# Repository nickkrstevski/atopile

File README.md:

# atopile

Compiler for hardware - starting with PCBs

## Usage

There's not a lot here, because it's over at http://docs.atopile.io/

## Development

### Prerequisites / Installation

You'll need >= `python3.10` and `pip` (Use `brew`).

I'd strongly recommend developing within a `venv`

Since we'll be using this `venv` for both work within this tool directory and whatever projects you're using it on, I'd recommend creating something along the lines of an `atopile-workspace` or `ato-ws` directory somewhere, and then creating a `venv` in there. This means if you do something like a `git clean -xdf` to remove crud, you won't blow away your `venv` with it.

If you decide to follow this, you'll end up with something like this:

```
atopile-workspace
├── .venv --> your virtual environment
├── atopile --> this repo
├── atopile.code-workspace --> vscode workspace file
└── bike-light --> project using atopile
```

Clone this repo.

Wherever you stick the `venv`, you can create the venv with  `python3.11 -m venv .venv` and then `source .venv/bin/activate`

For cli development (so practically all the time) : `pip install -e ."`

You'll need `npm` for front-end development (`brew install node`).

For any front-end development, you'll also need to install the front-end dependencies: `npm install`

## CLI development

ANTLR (or more specifically Java) was a PITA to get working on my Mac... so, I didn't 🤷‍♂️, I just wrapped up ANTLR in a neat little dockerised bundle and make a script that calls out to it easily.

As of writing, that lives in [mawildoer/antlr4](https://github.com/mawildoer/antlr4/tree/mawildoer/simplified-portable-docker/docker-simplified), but [hopefully we can get it into ANTLR mainline](https://github.com/antlr/antlr4/pull/4244) soon.

For now, clone the branch in the first link (eg. to your "repos" or "projects" directory), and then follow the [instructions](https://github.com/mawildoer/antlr4/tree/mawildoer/simplified-portable-docker/docker-simplified) on how to build it.

You can build the grammer to python source with the following command (modified with the appropriate paths for you).

`cd src/atopile/parser`

`/Users/mattwildoer/Projects/antlr4/docker-simplified/antlr4 -Dlanguage=Python3 -visitor AtopileParser.g4 AtopileLexer.g4`

## Front end development

To check out front-end changes live, run `npm run serve` in one terminal and make sure to run `ato view` on a project in another (to provide API access).

This will start the front-end server at `localhost:1234` and the backend at `localhost:2860`. The front-end's development server (`pracel`) will proxy API requests to the backend.

## Syntax highlighting is pretty nice...

You can download the extension from CI here:

Then, from your PC `code --install-extension path/to/atopile-*.vsix`

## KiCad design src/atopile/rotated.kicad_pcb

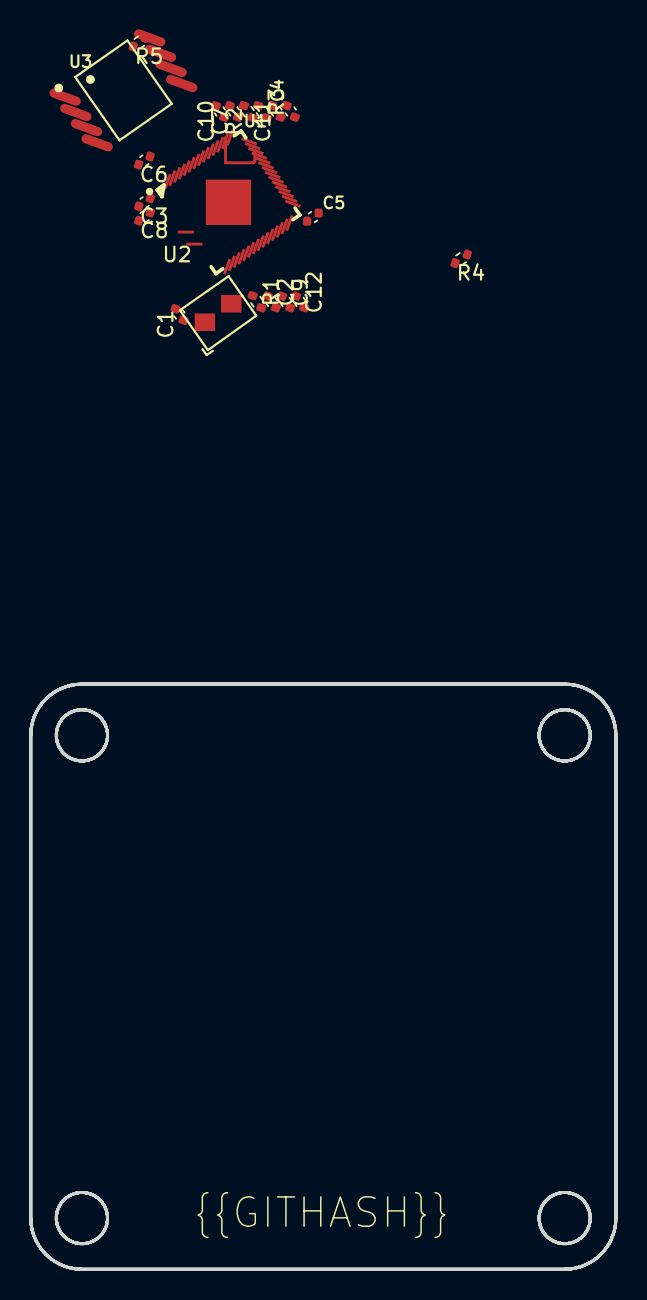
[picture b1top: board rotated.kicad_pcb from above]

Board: 2 copper layers, 40.0 x 40.0 mm, 20 parts (0 on the bottom side), 15 nets.

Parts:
C1, C2: 20pF; C0402
C3, C4, C5, C6, C7, C9, C10, C11: 100nF; C0402
C8, C12: 1uF; C0402
R1: 1k; R0402
R2, R3: 27R; R0402
R4, R5: 10k; R0402
U1: <help! no value>; LQFN-56_L7.0-W7.0-P0.4-EP
U2: <help! no value>; OSC-SMD_4P-L3.2-W2.5-BL
U3: <help! no value>; SOIC-8_L5.3-W5.3-P1.27-LS8.0-BL

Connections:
cs: R5.2, U1.56, U3.1
gnd: C1.2, C2.2, C3.2, C4.2, C5.2, C6.2, C7.2, C8.2, C9.2, C10.2, C11.2, C12.2, U1.19, U1.57, U2.2, U2.4, U3.4
io0: U1.53, U3.5
io1: U1.55, U3.2
io2: U1.54, U3.3
io3: U1.51, U3.7
out: R1.2, U2.3
p1: C2.1, R1.1, U1.21
run: R4.2, U1.26
sck: U1.52, U3.6
usb_dm: R3.2, U1.46
usb_dp: R2.1, U1.47
vcc: C3.1, C4.1, C5.1, C6.1, C7.1, C8.1, R4.1, R5.1, U1.1, U1.10, U1.22, U1.33, U1.42, U1.43, U1.44, U1.48, U1.49, U3.8
vcc-1: C9.1, C10.1, C11.1, C12.1, U1.23, U1.45, U1.50
xin: C1.1, U1.20, U2.1

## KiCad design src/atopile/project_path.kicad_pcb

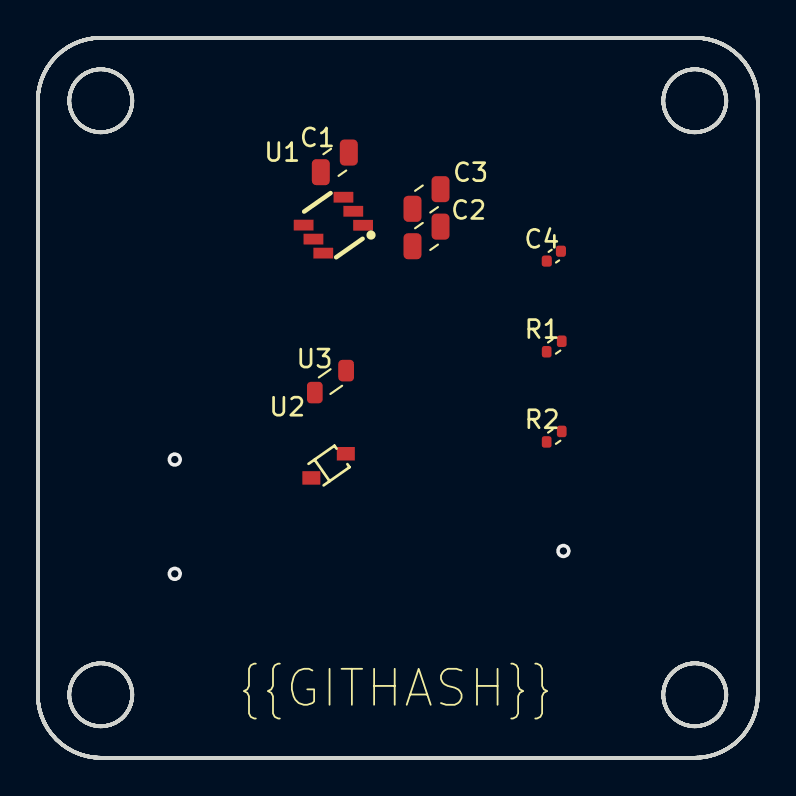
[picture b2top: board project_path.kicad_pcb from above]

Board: 2 copper layers, 40.0 x 40.0 mm, 9 parts (0 on the bottom side), 6 nets, no tracks yet.

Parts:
C1, C2, C3: 10uF; C0805
C4: 100nF; C0402
R1: 147K; R0402
R2: 10K; R0402
U1: <help! no value>; SOT-23-6_L2.9-W1.6-P0.95-LS2.8-BR
U2: <help! no value>; SOD-323_L1.8-W1.3-LS2.5-RD
U3: <help! no value>; L0805

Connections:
cb: C4.1, U1.1
gnd: C1.2, C2.2, C3.2, R2.2, U1.2, U2.2
out: R1.2, R2.1, U1.3
sw: C4.2, U1.6, U2.1, U3.1
vcc: C1.1, U1.4, U1.5
vcc-1: C2.1, C3.1, R1.1, U3.2

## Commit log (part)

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2023-04-18 checkpoint for Tim to look at
2023-04-18 checkpoint 2
2023-04-18 tidy
2023-04-19 manually generate resistors in data/sandbox1_resistors.py
2023-04-19 add object and parent attributes to graph nodes
2023-04-21 checkpoint on 1st iteration graphs
2023-04-22 add sandbox datamodel3
2023-04-22 work up some larger functions
2023-04-22 play with netlist generation
2023-04-22 create functions to find a vertex from a path, find a root vertex and add a block
2023-04-22 move methods to src
2023-04-22 whos your daddy?
2023-04-22 whos your daddy returns a index instead of a list
2023-04-22 add options to plot and make ancestory_dot_com work
2023-04-22 add some notes
2023-04-22 move data into atopile dir
2023-04-22 move resistor into data
2023-04-22 refactor model directory
2023-04-22 Add netlist generator
2023-04-22 more helper functions
2023-04-22 remove sandboxed turds
2023-04-27 Trying to instantiate elements
2023-04-28 add 555.ato
2023-04-29 add create vertex function
2023-05-04 langauge checkpoint 1
2023-05-13 clean up parsing after adding imports
2023-05-21 basis of cascading vis_configs
2023-05-21 cachemanager works as intended, but it seems like the tree from ANTLR isn't pickleable
2023-05-21 take at tidying stub rendering, not working
2023-06-04 build and publish docs in CI
2023-06-04 test
2023-06-04 test 2
2023-06-04 ci test
2023-06-14 update size based on number of ports
2023-06-14 combine resize functions together
2023-06-14 remove deprecated code
2023-06-14 resize based on text
2023-06-14 make labels vertical
2023-06-14 improve font size
2023-06-20 checkpoint towards netnaming
2023-06-26 find the module .ato file
2023-06-26 new file is being created
2023-06-27 rendre_script mods
2023-06-27 create some basic view infra
2023-06-28 kaniko CI
2023-06-28 scm patch
2023-06-28 kaniko patch
2023-06-28 patch
2023-06-28 find the position based on ato file
2023-07-05 checkpoint
2023-07-10 checkpoint - kicad doesn't seem to display fields well
2023-07-13 Frist, tidy up
2023-07-13 refactor testing
2023-07-13 All tests back to passing
2023-07-13 fix render test
2023-07-13 use new resolve name
2023-07-13 Add names to links and test
2023-07-13 add xfail test-case to draft flipped naming tests
2023-07-13 Test update dict
2023-07-14 update configs tested
2023-07-14 Homogonise ato post paths
2023-07-14 She runs!
2023-07-19 Add spec to give pins integer names
2023-07-19 Support integer pin references
2023-07-24 checkpoint - added second visitor and thread pool
2023-07-24 shitty parallel parser
2023-07-25 glob selectors and switch operators
2023-07-27 let me show you it's features
2023-07-28 add example file
2023-07-28 add comments and fix type
2023-07-28 start populating the examples
2023-07-28 add some math to the vdiv
2023-07-29 rename language spec
2023-07-29 part way though resistor divider example
2023-07-31 update gitignore for parcel
2023-07-31 update client files for parcel
2023-07-31 add parcel files
2023-08-01 Add LDO example
2023-08-02 position of modules is updated
2023-08-03 language workshopping w/ Tim
2023-08-03 basic rev2 parser building
2023-08-04 clarify rules
2023-08-04 sandbox/language-development/keywords.ato
2023-08-05 clean the rules for component asignement
2023-08-09 tweak a few aspects
2023-08-09 add package.json
2023-08-09 Modualisation with revserse-proxy working
2023-08-09 Rename visualizer to viewer and serve from dist directory
2023-08-09 Build viewer in CI
2023-08-09 temp - check CI python package
2023-08-09 add needs between cli and viewer
2023-08-09 Take files from dist as default for dev installs, or from src/atopile/viewer/static for regular installs Add static viewer for current cloned peeps
2023-08-09 Package static with builds
2023-08-10 Make moves towards static install - no there yet, for std lib reasons
2023-08-10 return CI to expected state
2023-08-10 Improve docs and make server updates
2023-08-11 Add netlist import info
2023-08-11 few fixes
2023-08-12 play with nets
2023-08-12 remove static turds
2023-08-13 checkpoint: ready to add actual replacement in builder
2023-08-16 Add target for static schematic view, "sch-view"
    This allows us to statically compile these assets in CI,
    host them as build-artifacts and embed them in PRs or documents.
    This commit only implements the backend for this (cli usage),
    not the front-end changes required to do the viewing.
2023-08-16 Add interfaces to atopile!
    Currently there's some hackiness in our communication with the viewer.
    The viewer does string manipulation on the paths, expecting to split them on .s
    however, it doesn't currently support handling interfaces as a block. We
    therefore we dash-join all the interface pins and place them on their parent component.
2023-09-17 Ruff in CI
2023-09-18 Do linting all the time
2023-09-23 Fix subclassing a module as a component. This is critical so replace a generic implementation of something with a concrete one.
    Specifically achieved this by replacing acknoledging the root node in the differ module and modifying node types for things that appear in the diff.
2023-09-24 Add get_data MVV helper function
2023-09-24 Make superclasses helper lazy
2023-09-24 Iter over class if instance
2023-09-25 Fix unit tests considering instace vs. class vs. superclass changes
2023-09-25 Use relative path references by default in the designators file
2023-10-02 mathematical scribbling
2023-10-06 remove root-node from config
2023-10-15 remove unused module
2023-10-15 modify render for variable depth
2023-10-15 Parser working
2023-10-15 New model types created
2023-10-17 hacky example
2023-10-17 mostly drafted compiler
2023-10-19 slow progress is progress none-the-less
2023-10-21 create intermediate data model models and skeletons
2023-10-22 Add data model descriptions
2023-10-22 start building the data model 1
2023-10-22 Add parsing test tools
2023-10-22 Rename Errors
2023-10-22 change the datamodel1 stracture
2023-10-22 Consolidate to refs
2023-10-22 Convert top supers references to string literal
2023-10-22 Remove sentinal types from datamodel1 - everything is by reference anyway
2023-10-22 Replace sentinals with literals
2023-10-22 Make literals consistent
2023-10-23 updates to datamodel1
2023-10-23 update the types
2023-10-23 add some testing and more resolution
2023-10-23 skeleton for dm2
2023-10-24 modules working
2023-11-10 update tests
2023-11-10 model 1 tests are passing
2023-11-10 update deps
2023-11-10 test integer
2023-11-10 testing connect statements
2023-11-11 change parser test structure
2023-11-11 currently broken
2023-11-12 add tuple for names
2023-11-12 assign statements
2023-11-12 tree vis class
2023-11-12 wrap file into object
2023-11-12 forgot
2023-11-12 fix children tuple return
2023-11-12 remove tuple from visitChildren()
2023-11-12 demand python3.11
2023-11-12 not sure we need this anymore, but sabing tweaks
2023-11-12 update error names
2023-11-12 datamodel2 splits between creating dm1-oriented frames and ChainMaps, and building all the dm2 trees
2023-11-13 tree visualizer working
2023-11-13 fix locals as tuple
2023-11-13 tree vis improvements - added links and replacement operator
2023-11-13 seems to be working
2023-11-13 moved dm1 visualizer to dev directory
2023-11-13 bug fix
2023-11-13 Rehome parse utils and unwrap some references in dm1
2023-11-13 added a print method to dm1_vis
2023-11-13 format testing indents a little more cleanly
2023-11-13 unwrap visitChildrenTuple a little
2023-11-13 added handler for _Sentinel.NOTHING in dm1_vis.py
2023-11-13 Rename scope things
2023-11-13 Basis for datamodel 2
2023-11-13 dm1 updates, created visit_iterable_helper to simplify returning multiple children from a ctx, fixed error in visitBlockDef test and visitModule1LayerDeep, both had mistakes in expected return, added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
2023-11-13 tidy up a little
2023-11-13 added test for interfaces, fixed visitBlocktype to add return case for interface type
2023-11-13 Tidy up
2023-11-13 structure dm2 conversion, but the name-lookup is still broken
2023-11-13 Rename basic testing functions
2023-11-13 Fixed file and import handling in dm1_vis
2023-11-14 Add src info to datamodels
2023-11-14 Add missing src info to dm1
2023-11-14 Rename testing
2023-11-14 added logic to handle pins as integers to the dm1_vis
2023-11-14 added string handling to dm1_vis, fixed pin as integer issue in dm1
2023-11-14 Working dm1 name resolution
2023-11-14 cleanup
2023-11-15 append to docs
2023-11-15 missed a new line before bullet points
2023-11-15 kicad plugin sad times
2023-11-15 whoops, reverting doc changes
2023-11-15 Scaffolding for easyeda2ato. Stopped due to AGPLv3 license on project.
2023-11-17 finds unique footprint library paths, creates a new library name for each path
2023-11-17 need to offset paths of nested junk
2023-11-17 Fix SyntaxError handling
2023-11-17 Hacky fix to layer BoM selections
2023-11-17 Fix dumb bug in case the ato project contains the ato compiler. This could occur if you have a .venv inside your project directory
2023-11-17 Standardised paths should be module-relative if in module.
2023-11-17 remove development scaffolding
2023-11-21 getting neighbors
2023-11-21 outline
2023-11-22 add some comments for handover
2023-11-22 removed push to git feature
2023-11-22 added some logging info for how to commit
2023-11-22 datastruct created
2023-11-23 checkpoint2
2023-11-23 removed dev,test,docs - all dependencies installed every time
2023-11-25 move code to viewer
2023-11-26 move the yosys netlist generation to targets
2023-11-26 need to clusterize and handle in process_block
2023-11-27 Dev containers -- experimental
2023-11-27 Use latest Kaniko debug image
2023-11-27 Use pep-0440-compliant versioning
2023-11-27 Smoosh user image onto dev image and ignore for now
2023-11-27 Run only on release
2023-11-27 Remove dev container configuration for atopile project itself
2023-11-27 add tutorial to docs
2023-11-27 Add forked easyeda2kicad dep
2023-12-03 equations sandbox
2023-12-03 cleanup of equations sandbox
2023-12-03 fixing paths for ato yaml after project template refactor
2023-12-04 simple solver
2023-12-04 playing about with tollerances
2023-12-04 playing with tollerances
2023-12-04 added feature to install from packages library and store dependencies in ato.yaml
2023-12-05 added a whole lotta features
2023-12-05 append to solver
2023-12-07 bottom up information
2023-12-08 add .ato/modules to search paths
2023-12-09 quick spin at component selector
2023-12-11 fix csv package format
2023-12-11 actually fix it
2023-12-11 Add debugpy flag to complier's common args
2023-12-11 I reckon this fixes the replacement operator
2023-12-11 Remove unrelated changes
2023-12-11 Downgrade colliding footprint warnings to debug
2023-12-11 Report all the designators associated with a row
2023-12-11 Make BoM lines unique for uniqueish components
2023-12-11 Remove hold-over-generic naming logic
2023-12-11 Add 100nF, 10uF and 1uF caps
2023-12-11 Fix bare except causing linting error
2023-12-11 add easyeda2ato and remove easyeda2kicad
2023-12-11 install error messages get displayed
2023-12-11 fix cli
2023-12-11 install will update the deps
2023-12-11 fix lint
2023-12-11 Add upgrade flag
2023-12-11 Repair bad merge
2023-12-13 Refactor error handling and logging
2023-12-13 Add title and addr info to base AtoError
2023-12-13 Default to empty message
2023-12-13 Downgrade missing footprints to warning
2023-12-13 Patch backwards exception from_ctx
2023-12-13 Handle exception for missing overrides
2023-12-13 Fix linting errors
2023-12-13 Add error accumulator helper
2023-12-13 Add tests for deffered error handling
2023-12-13 Suppress click frames from tracebacks in debug
2023-12-13 Split formatting and error logging functions. Format errors with some ~~pezzaz~~
2023-12-13 Add downgrade function to reduce errors to warnings or similar and stop their propagation up the callstack
2023-12-13 Use standardised error handling for netlist and BoM generation
2023-12-13 Name targets
2023-12-13 Remove unused MagicMock
2023-12-14 playing about
2023-12-14 testing rotation
2023-12-15 layout reuse progress
2023-12-19 Flip command around
2023-12-19 Disable other jobs
2023-12-19 change ci
2023-12-21 mid-development of equations
